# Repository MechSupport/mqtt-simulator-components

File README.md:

# mqtt-simulator-components
Components that use MQTT to quickly and efficiently build full or partial cockpit simulators.

# What is this project?
This project will create modular devices and designs for a variety of similator systems. The overall intent of the project is to reduce the amount of time needed to make a simulator from months-years to days. To do this, the simulator needs to be broken into modular parts that can be quickly programmed and connected.

# What are the components?
The simulator architecture is broken into four discrete elements consisting of; the *simulator software*; the *MQTT server*; the *panel controller*, and; the *input/output devices*.

## Simulator Software
This is the software that runs the simulation. Note that this does not have to be intentionally designed as a simulator. The software chosen for the initial build of this system was Mechwarrior 5: Mercenaries, as it has many controls and a good support system through both modders and the original developers.

## MQTT Server
This is a standard MQTT server. It takes information from the simulator software and provides it to the panel controllers via IP messages.

## Panel Controller
The panel controller connects the I/O devices to the ethernet network. It can be either an off the shelf RPi, an ESP32 or any other IoT device with SPI support. It operates as the SPI master while the I/O devices are the SPI slaves.

The name 'Panel Controller' comes from the physical layout of a cockpit. Panels are sections of the cockpit that have similar gauges or switches, all affixed to one solid surface. Each of these surfaces would have a dedicated panel controller that is then connected to the network.

## Input / Output Devices
These are the actual devices that the user can interact with. They either show the status of the simulation or act as a human interface device for controlling the simulation. Each device (or sub-panel, in the case of switches or button boxes) has their own microcontroller that communicates with the panel controller via SPI. The device holds the name of the MQTT address and server IP that it is looking for in EEPROM and communicates it to the Panel Controller via SPI. The Panel Controller fetches this data and sends it back to the I/O device.

# Examples:
## Altimeter
This is an example of a simple dial indicator. It would be constructed using a pair of servo motors connected together using a gear train to enable both needles to move independently. It requests the current altitude from the server and displays accordingly.

Altimeter -> Requests /data/altitude from Panel Controller

Panel Controller -> Requests /data/altitude from MQTT server

MQTT -> Sends 10500 to Panel Controller

Panel Controller -> Sends 10500 to Altimeter via SPI

Altimeter -> Updates needle location

Note: The server software is being updated by the simulator at 20-60Hz

## Multi-Function Display (MFD)
This is an example of a multi-function display commonly found in fighter aircraft. It is a square screen used for showing maps with buttons around the perimeter for changing map settings.

MFD -> Receives button press fom user, requests /map from Panel Controller

Panel Controller -> Requests /map from MQTT server

MQTT -> Sends map.png to Panel Controller

Panel Controller -> Sends map.png to MFD via SPI

Altimeter -> Updates screen display

Note: In this case the MFD's microcontroller would require more performance than the previous example. Something like a RPi Zero/2 W
Note 2: This is approaching a solution where a RPi could be used for both the Panel Controller and the IO device are integrated together

## Toggle Switch Array
This is an example of a set of toggle switches for changing system settings in the simulation. In this case, it is an open loop feedback control as no response is required from the server.

TSA -> Receives button press fom user, sends key "F4" to Panel Controller

Panel Controller -> sends key "F4" to /inputControl on MQTT server

MQTT Server -> Emulates "F4" keypress, clears /inputControl for next emulated command

Note: If the server is not running on the simulator computer, a small client will need to be running on the simulator computer that reads /inputControl and emulates keypresses accordingly.

# Design Principles

These principles are up for discussion, however the reasoning for including or not including them are stored here.

## Software / Communication Protocols

### MQTT
MQTT was implemented becuase it requires a small amount of computational and network traffic. Many microcontrollers with built in WiFi or Ethernet have MQTT support in their libraries and a plethora of documentation on how to make them IoT connected.

## Physical Components

### EveryI/O Device Has a Microcontroller
A dedicated microcontroller for each I/O device increases the overall useability of the system while decreasing the number of connections from the panel controller to the I/O device. In essence, the microcontroller allows for serial communication over parallel for components that may have a large number of switches (e.g. MFD or buttonbox) or a complicated output (e.g. altimeter). The increase in cost for each I/O device is outweighed by the increase in modularity. 

This also means that a gauge could be unplugged from one panel controller, moved to another panel (or even another cockpit entirely if on the same network), and plugged in via the SPI connection and it would start to work right away.

##

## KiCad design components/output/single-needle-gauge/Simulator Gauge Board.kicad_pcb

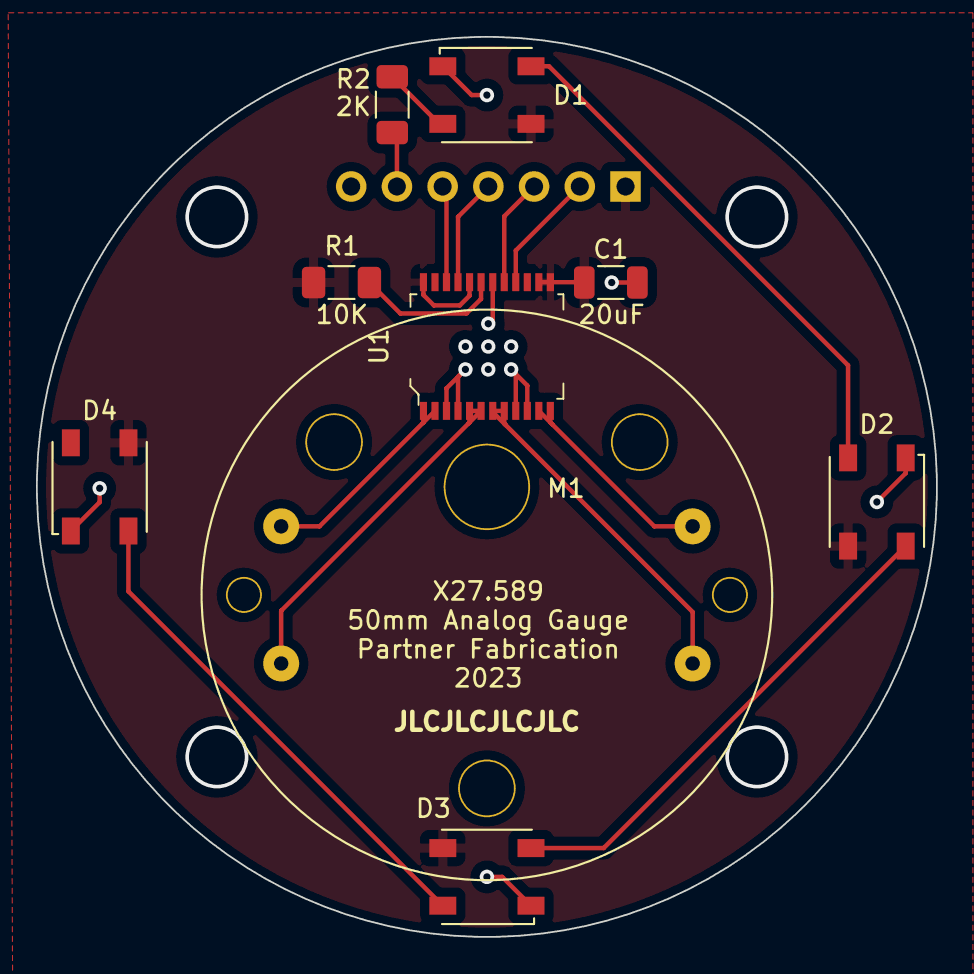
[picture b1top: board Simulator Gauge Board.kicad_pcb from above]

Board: 2 copper layers, 50.0 x 50.0 mm, 10 parts (1 on the bottom side), 16 nets.

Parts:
C1: 20uF; C_1206_3216Metric
D1, D2, D3, D4: Inolux_IN-PI554FCH; LED_Inolux_IN-PI554FCH_PLCC4_5.0x5.0mm_P3.2mm
J1: Conn_01x07_Female; PinHeader_1x07_P2.54mm_Vertical
M1: X27.168_Motor; X27.168 Stepper Motor
R1: 10K; R_1206_3216Metric_Pad1.30x1.75mm_HandSolder
R2: 2K; R_1206_3216Metric_Pad1.30x1.75mm_HandSolder
U1: TB6612FNG_C_8_EL; LSSOP-24_W5.6mm

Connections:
+5V: C1.1, D1.3 (VDD), D2.3 (VDD), D3.3 (VDD), D4.3 (VDD), J1.1, R1.2, U1.13 (VM2), U1.14 (VM3), U1.20 (VCC), U1.24 (VM1)
AI1: J1.4, U1.21 (AIN1)
AI2: J1.5, U1.22 (AIN2)
AO1: M1.1, U1.1 (AO1), U1.2 (AO1)
AO2: M1.2, U1.5 (AO2), U1.6 (AO2)
BI1: J1.3, U1.17 (BIN1)
BI2: J1.2, U1.16 (BIN2)
BO1: M1.4, U1.11 (BO1), U1.12 (BO1)
BO2: M1.3, U1.7 (BO2), U1.8 (BO2)
GND: C1.2, D1.1 (VSS), D2.1 (VSS), D3.1 (VSS), D4.1 (VSS), J1.7, U1.3 (PGND1), U1.4 (PGND1), U1.9 (PGND2), U1.10 (PGND2), U1.18 (GND)
LED_D: J1.6, R2.2
unnamed: D1.2 (DIN), R2.1
unnamed: D1.4 (DO), D2.2 (DIN)
unnamed: D2.4 (DO), D3.2 (DIN)
unnamed: D3.4 (DO), D4.2 (DIN)
unnamed: R1.1, U1.19 (STBY)

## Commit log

2023-04-10 Rename MQTTSimDiagram.svg to media/MQTTSimDiagram.svg
2023-04-10 Rename Simulator Gauge Board.kicad_pcb to components/output/single-needle-gauge/Simulator Gauge Board.kicad_pcb
2023-04-11 Added more detail
2023-04-11 Updated formatting
2023-04-13 added Generic Relay as output device
2023-04-13 spelling....sigh...
2023-04-14 created new gauge for mech warrior 5
